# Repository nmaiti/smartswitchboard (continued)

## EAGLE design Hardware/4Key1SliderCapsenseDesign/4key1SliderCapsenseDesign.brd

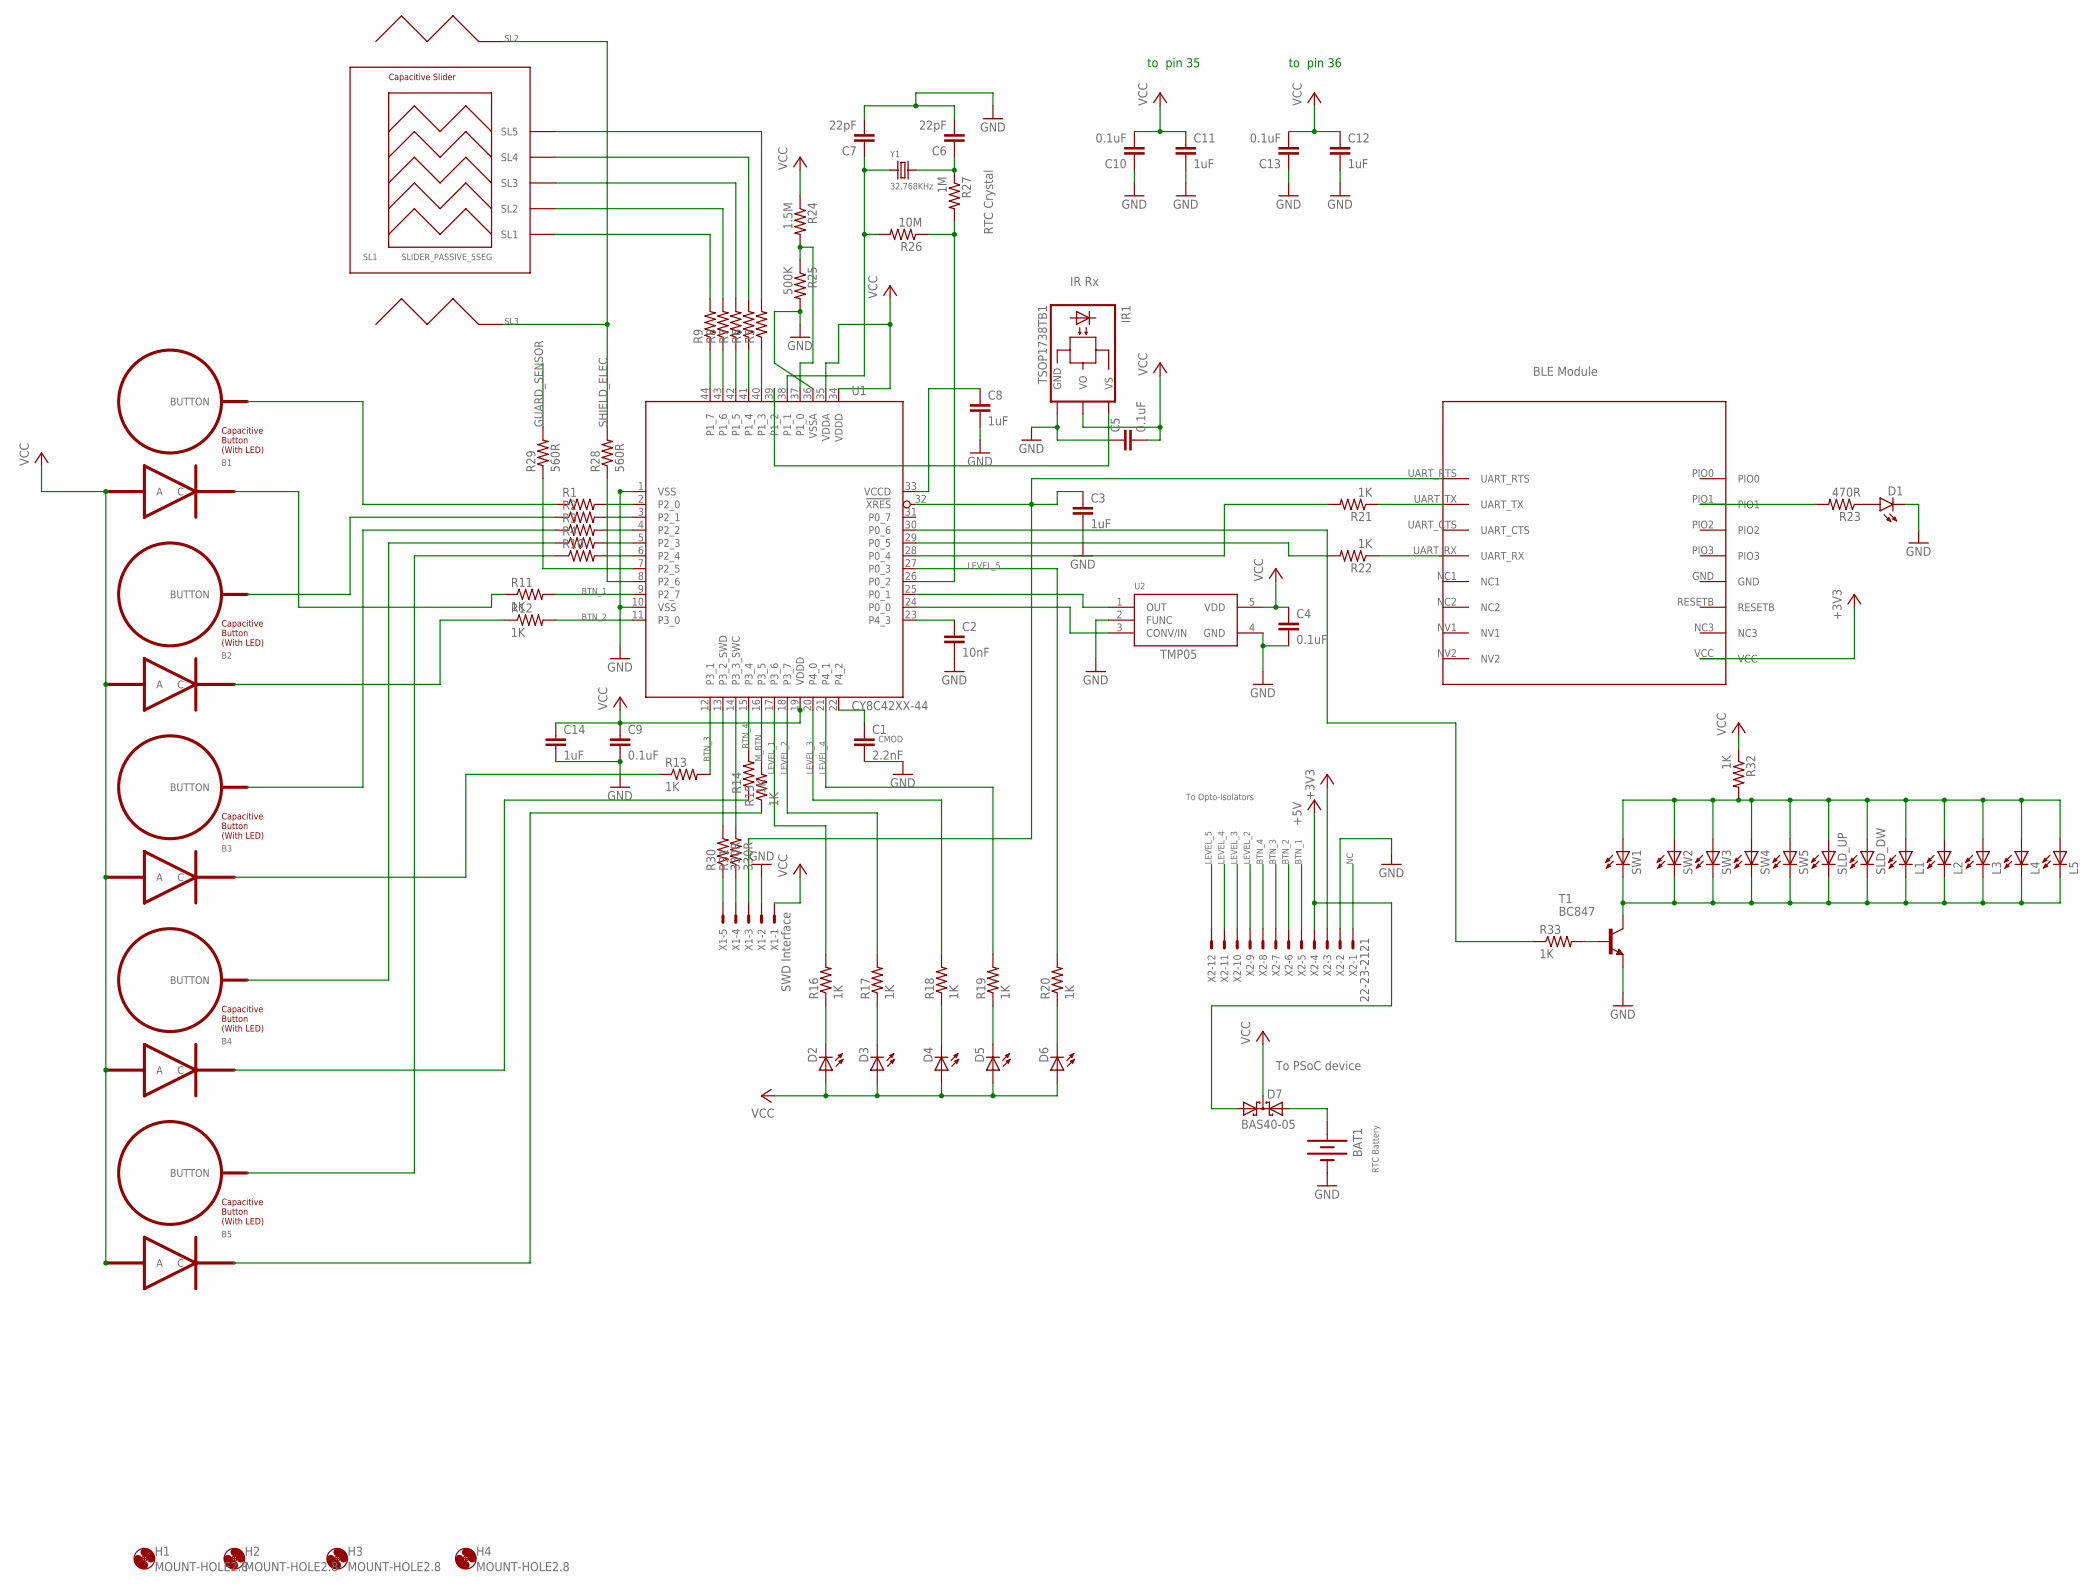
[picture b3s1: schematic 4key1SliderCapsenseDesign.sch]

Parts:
B1, B2, B3, B4, B5: BUTTON_PASSIVE_LED; BUTTON_PASSIVE_12MM_LED
BAT1: BATTERY245MM; BATTCON_245MM
C1: 2.2nF; 1206
C2: 10nF; 1206
C3, C8, C11, C12, C14: 1uF; 1206
C4, C5, C9, C10, C13: 0.1uF; 1206
C6, C7: 22pF; 1206
D1: LED1206-BOTTOM; LED-1206-BOTTOM
D2, D3, D4, D5, D6: LEDCHIP-LED0805; CHIP-LED0805
D7: BAS40-05; SOT23
H1, H2, H3, H4: MOUNT-HOLE2.8; 2,8
IR1: TSOP1738TB1; TSOP17_TB1
L1, L2, L3, L4, L5: LEDCHIPLED_1206; CHIPLED_1206
R1, R2, R3, R4, R5, R6, R7, R8, R9, R10: RESISTOR1206; 1206
R11, R12, R13, R14, R15, R16, R17, R18, R19, R20, R21, R22, R32, R33: 1K; 1206
R23: 470R; 1206
R24: 1.5M; 1206
R25: 500K; 1206
R26: 10M; 1206
R27: 1M; 1206
R28, R29: 560R; 1206
R30, R31: 330R; 1206
SL1: SLIDER_PASSIVE_5SEG; SLIDER_PASSIVE_5SEG_12MM
SL2, SL3: SLIDER_PASSIVE_1SEG; SLIDER_PASSIVE_1SEG_12MM
SLD_DW: LEDCHIPLED_1206; CHIPLED_1206
SLD_UP: LEDCHIPLED_1206; CHIPLED_1206
SW1, SW2, SW3, SW4, SW5: LEDCHIPLED_1206; CHIPLED_1206
T1: BC847; SOT23
U1: CY8C42XX-44; TQFP-10X10-44
U2: NCP1400A_STEPUP; SOT23-5
U$1: HM-11
X1: SWD Interface; 22-23-2051
X2: 22-23-2121
Y1: 32.768KHz; CRYSTAL_CYL_2X6MM_SMT

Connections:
+3V3: U$1.VCC, X2.3
+5V: D7.1 (A1), X2.4
BTN_1: R11.2, U1.9 (P2_7), X2.5
BTN_2: R12.2, U1.11 (P3_0), X2.6
BTN_3: R13.2, U1.12 (P3_1), X2.7
BTN_4: R14.2, U1.15 (P3_4), X2.8
GND: BAT1.2 (-), C1.2, C2.2, C3.2, C4.2, C5.1, C6.2, C7.2, C8.2, C9.2, C10.1, C11.2, C12.2, C13.1, C14.2, D1.C, IR1.GND, R25.2, T1.2 (E), U1.1 (VSS), U1.10 (VSS), U1.36 (VSSA), U2.2 (FUNC), U2.4 (GND), X1.2, X2.2
GUARD_SENSOR: R29.1, R29.2, U1.7 (P2_5)
LEVEL_1: R16.2, U1.17 (P3_6)
LEVEL_2: R17.2, U1.18 (P3_7), X2.9
LEVEL_3: R18.2, U1.20 (P4_0), X2.10
LEVEL_4: R19.2, U1.21 (P4_1), X2.11
LEVEL_5: R20.2, U1.27 (P0_3), X2.12
M_BTN: R15.2, U1.16 (P3_5)
unnamed: C1.1, U1.22 (P4_2)
unnamed: R1.2, U1.2 (P2_0)
unnamed: C2.1, U1.23 (P4_3)
unnamed: R2.2, U1.3 (P2_1)
unnamed: R3.2, U1.4 (P2_2)
unnamed: R4.2, U1.5 (P2_3)
unnamed: B1.BUTTON, R1.1
unnamed: B2.BUTTON, R2.1
unnamed: B3.BUTTON, R3.1
unnamed: B4.BUTTON, R4.1
unnamed: R10.2, U1.6 (P2_4)
unnamed: B5.BUTTON, R10.1
unnamed: R5.1, U1.40 (P1_3)
unnamed: R6.1, U1.41 (P1_4)
unnamed: R7.1, U1.42 (P1_5)
unnamed: R8.1, U1.43 (P1_6)
unnamed: R9.1, U1.44 (P1_7)
unnamed: R9.2, SL1.SL1
unnamed: R8.2, SL1.SL2
unnamed: R7.2, SL1.SL3
unnamed: R6.2, SL1.SL4
unnamed: R5.2, SL1.SL5
unnamed: R28.1, U1.8 (P2_6)
unnamed: B1.C, R11.1
unnamed: B2.C, R12.1
unnamed: B3.C, R13.1
unnamed: B4.C, R14.1
unnamed: B5.C, R15.1
unnamed: R30.2, U1.13 (P3_2_SWD)
unnamed: C8.1, U1.33 (VCCD)
unnamed: R30.1, X1.5
unnamed: R31.2, U1.14 (P3_3_SWC)
unnamed: R31.1, X1.4
unnamed: L1.A, L2.A, L3.A, L4.A, L5.A, R32.2, SLD_DW.A, SLD_UP.A, SW1.A, SW2.A, SW3.A, SW4.A, SW5.A
unnamed: D2.C, R16.1
unnamed: L1.C, L2.C, L3.C, L4.C, L5.C, SLD_DW.C, SLD_UP.C, SW1.C, SW2.C, SW3.C, SW4.C, SW5.C, T1.3 (C)
unnamed: D3.C, R17.1
unnamed: R33.2, T1.1 (B)
unnamed: BAT1.1 (+), D7.2 (A2)
unnamed: C3.1, U1.32 (!XRES), U$1.UART_RTS, X1.3
unnamed: R21.1, U$1.UART_TX
unnamed: R33.1, U1.30 (P0_6)
unnamed: R22.1, U$1.UART_RX
unnamed: R21.2, U1.28 (P0_4)
unnamed: R22.2, U1.29 (P0_5)
unnamed: D1.A, R23.1
unnamed: U1.24 (P0_0), U2.3 (CONV/IN)
unnamed: R23.2, U$1.PIO1
unnamed: U1.25 (P0_1), U2.1 (OUT)
unnamed: IR1.VS, U1.39 (P1_2)
unnamed: R24.2, R25.1, U1.37 (P1_0)
unnamed: R26.1, R27.2, U1.26 (P0_2)
unnamed: C6.1, R27.1, Y1.2
unnamed: C7.1, R26.2, U1.38 (P1_1), Y1.1
unnamed: D6.C, R20.1
unnamed: D5.C, R19.1
unnamed: D4.C, R18.1
NC: X2.1
SHIELD_ELEC: R28.2, SL2.S1, SL3.S1
VCC: B1.A, B2.A, B3.A, B4.A, B5.A, C4.1, C5.2, C9.1, C10.2, C11.1, C12.1, C13.2, C14.1, D2.A, D3.A, D4.A, D5.A, D6.A, D7.3 (C), IR1.VO, R24.1, R32.1, U1.19 (VDDD), U1.34 (VDDD), U1.35 (VDDA), U2.5 (VDD), X1.1

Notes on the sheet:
CMOD
TMP05
To Opto-Isolators
IR Rx
BLE Module
RTC Crystal
to pin 36
to pin 35
To PSoC device
RTC Battery

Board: 2 copper layers, 87 parts (35 on the bottom side), 73 nets, no tracks yet.

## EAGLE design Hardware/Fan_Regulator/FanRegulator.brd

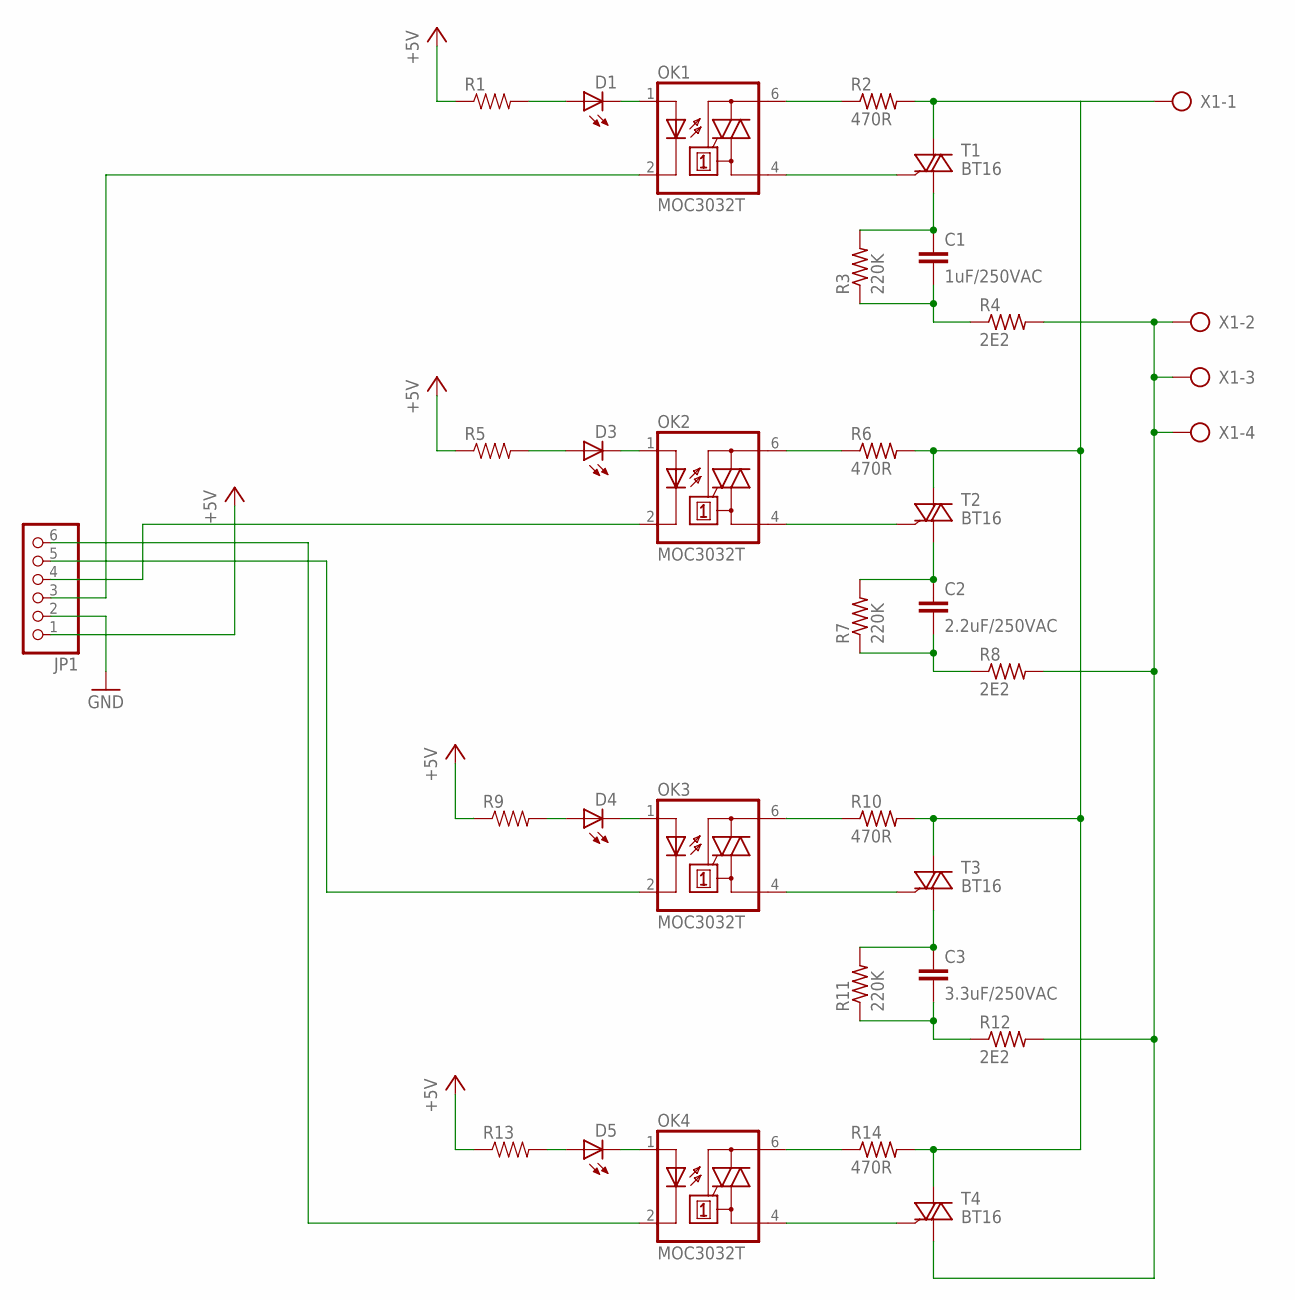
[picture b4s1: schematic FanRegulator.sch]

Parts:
C1: 1uF/250VAC; C27.5B9
C2: 2.2uF/250VAC; C27.5B9
C3: 3.3uF/250VAC; C27.5B9
D1, D3, D4, D5: LED3MM
JP1: PINHD-1X6; 1X06
OK1, OK2, OK3, OK4: MOC3032T; DIL06B
R1, R5, R9, R13: RESISTOR1206; 1206
R2, R6, R10, R14: 470R; R0207/1V
R3, R7, R11: 220K; R0207/1V
R4, R8, R12: 2E2; R0207/1V
T1, T2, T3, T4: BT16; TO220BV
X1: AK300/4

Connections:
+5V: JP1.1, R1.1, R5.1, R9.1, R13.1
GND: JP1.2
unnamed: OK1.6 (A2), R2.1
unnamed: OK1.4 (A1), T1.G
unnamed: D1.A, R1.2
unnamed: C1.1, R3.2, T1.T1 (A1)
unnamed: C1.2, R3.1, R4.1
unnamed: D1.K (C), OK1.1 (A)
unnamed: D3.A, R5.2
unnamed: JP1.3, OK1.2 (C)
unnamed: OK2.6 (A2), R6.1
unnamed: OK2.4 (A1), T2.G
unnamed: R2.2, R6.2, R10.2, R14.2, T1.T2 (A2), T2.T2 (A2), T3.T2 (A2), T4.T2 (A2), X1.1
unnamed: C2.1, R7.2, T2.T1 (A1)
unnamed: C2.2, R7.1, R8.1
unnamed: D3.K (C), OK2.1 (A)
unnamed: D4.A, R9.2
unnamed: JP1.4, OK2.2 (C)
unnamed: OK3.6 (A2), R10.1
unnamed: OK3.4 (A1), T3.G
unnamed: D4.K (C), OK3.1 (A)
unnamed: C3.1, R11.2, T3.T1 (A1)
unnamed: C3.2, R11.1, R12.1
unnamed: D5.A, R13.2
unnamed: D5.K (C), OK4.1 (A)
unnamed: JP1.5, OK3.2 (C)
unnamed: OK4.6 (A2), R14.1
unnamed: OK4.4 (A1), T4.G
unnamed: JP1.6, OK4.2 (C)
unnamed: R4.2, R8.2, R12.2, T4.T1 (A1), X1.2, X1.3, X1.4

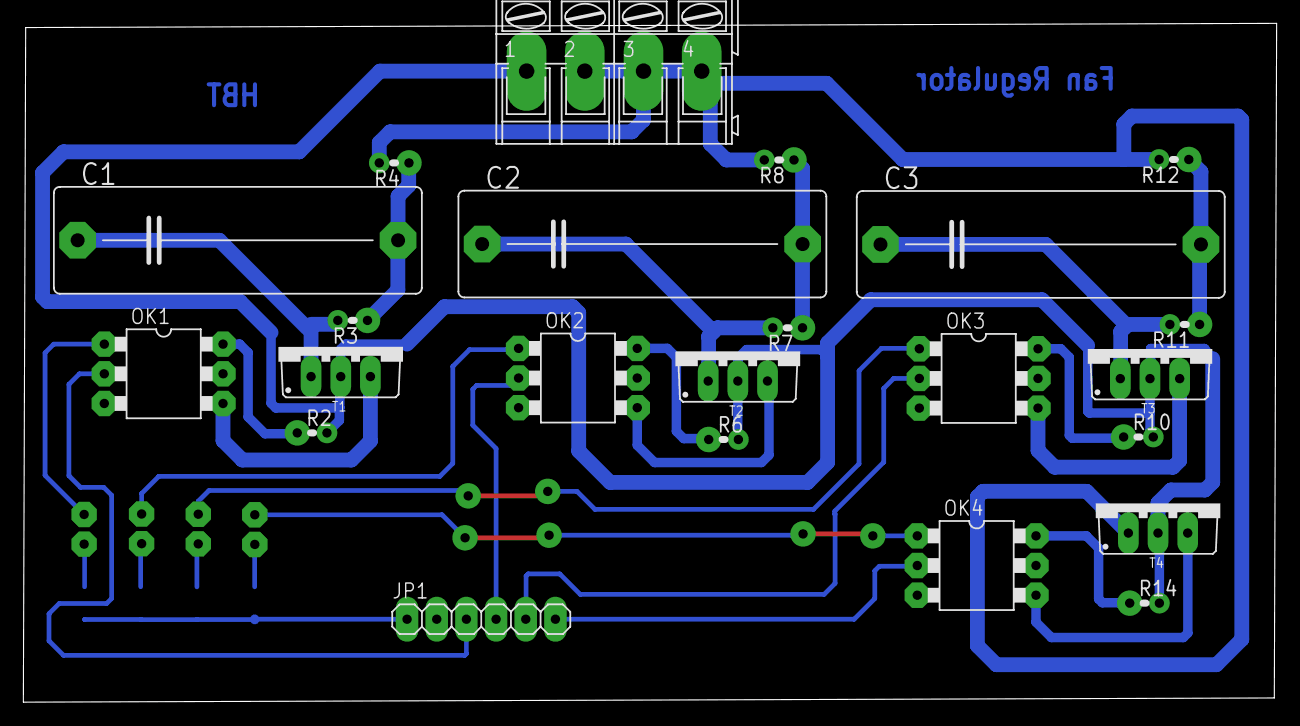
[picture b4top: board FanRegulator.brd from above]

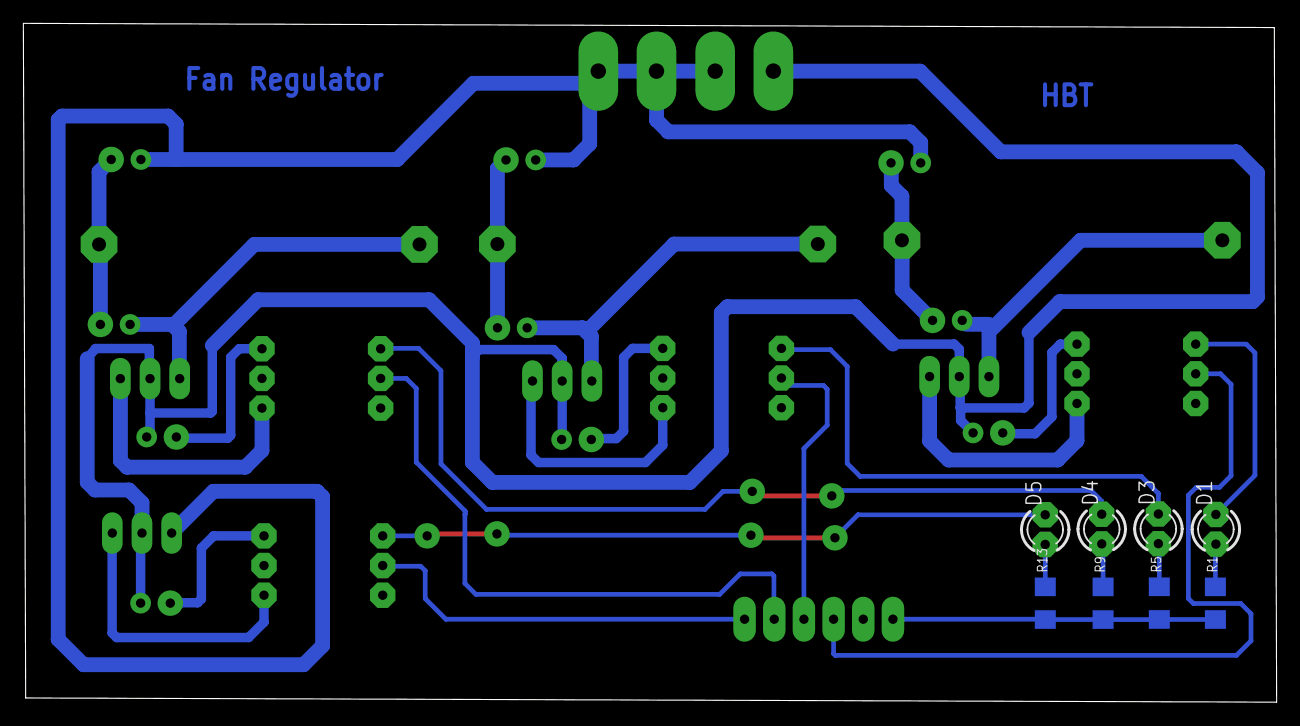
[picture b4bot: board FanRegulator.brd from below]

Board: 2 copper layers, 107.3 x 58.1 mm, 31 parts (8 on the bottom side), 29 nets.

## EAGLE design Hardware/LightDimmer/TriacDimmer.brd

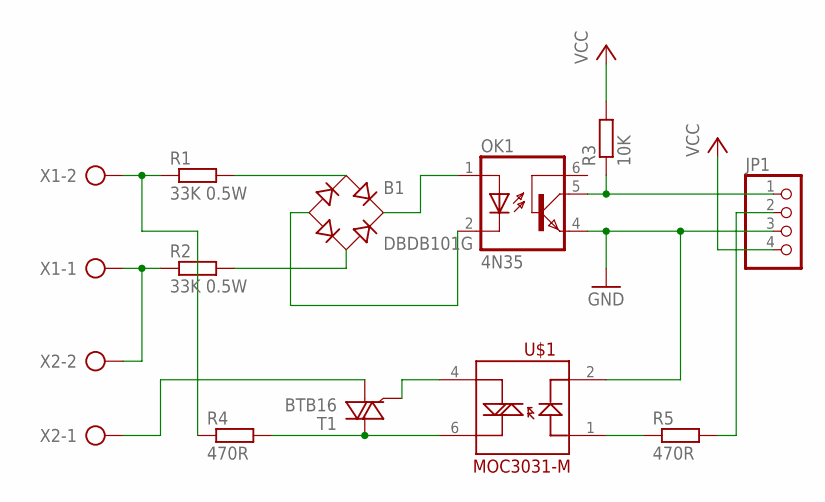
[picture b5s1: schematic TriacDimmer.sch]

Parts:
B1: DBDB101G; DB
JP1: PINHD-1X4; 1X04
OK1: 4N35; DIL06
R1, R2: 33K 0.5W; 0207/10
R3: 10K; 0207/10
R4, R5: 470R; 0207/10
T1: BTB16; TO220BV
U$1: MOC3031-M; DIL06
X1, X2: AK300/2

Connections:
GND: JP1.3, OK1.4 (EMI), U$1.2
unnamed: R1.1, R4.1, X1.2
unnamed: R2.1, X1.1, X2.2
unnamed: B1.AC1, R1.2
unnamed: B1.AC2, R2.2
unnamed: B1.+, OK1.1 (A)
unnamed: B1.-, OK1.2 (C)
unnamed: JP1.1, OK1.5 (COL), R3.1
unnamed: JP1.2, R5.2
unnamed: R4.2, T1.T2 (A2), U$1.6
unnamed: T1.G, U$1.4
unnamed: T1.T1 (A1), X2.1
unnamed: R5.1, U$1.1
VCC: JP1.4, R3.2

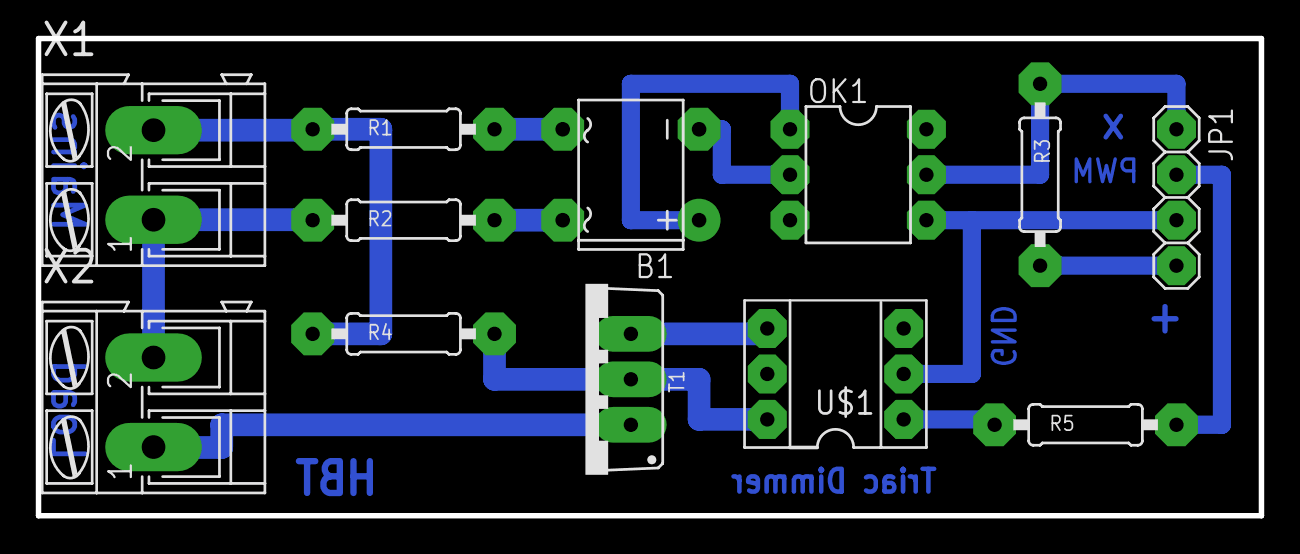
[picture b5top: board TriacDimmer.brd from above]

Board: 2 copper layers, 68.3 x 26.7 mm, 12 parts (0 on the bottom side), 14 nets.

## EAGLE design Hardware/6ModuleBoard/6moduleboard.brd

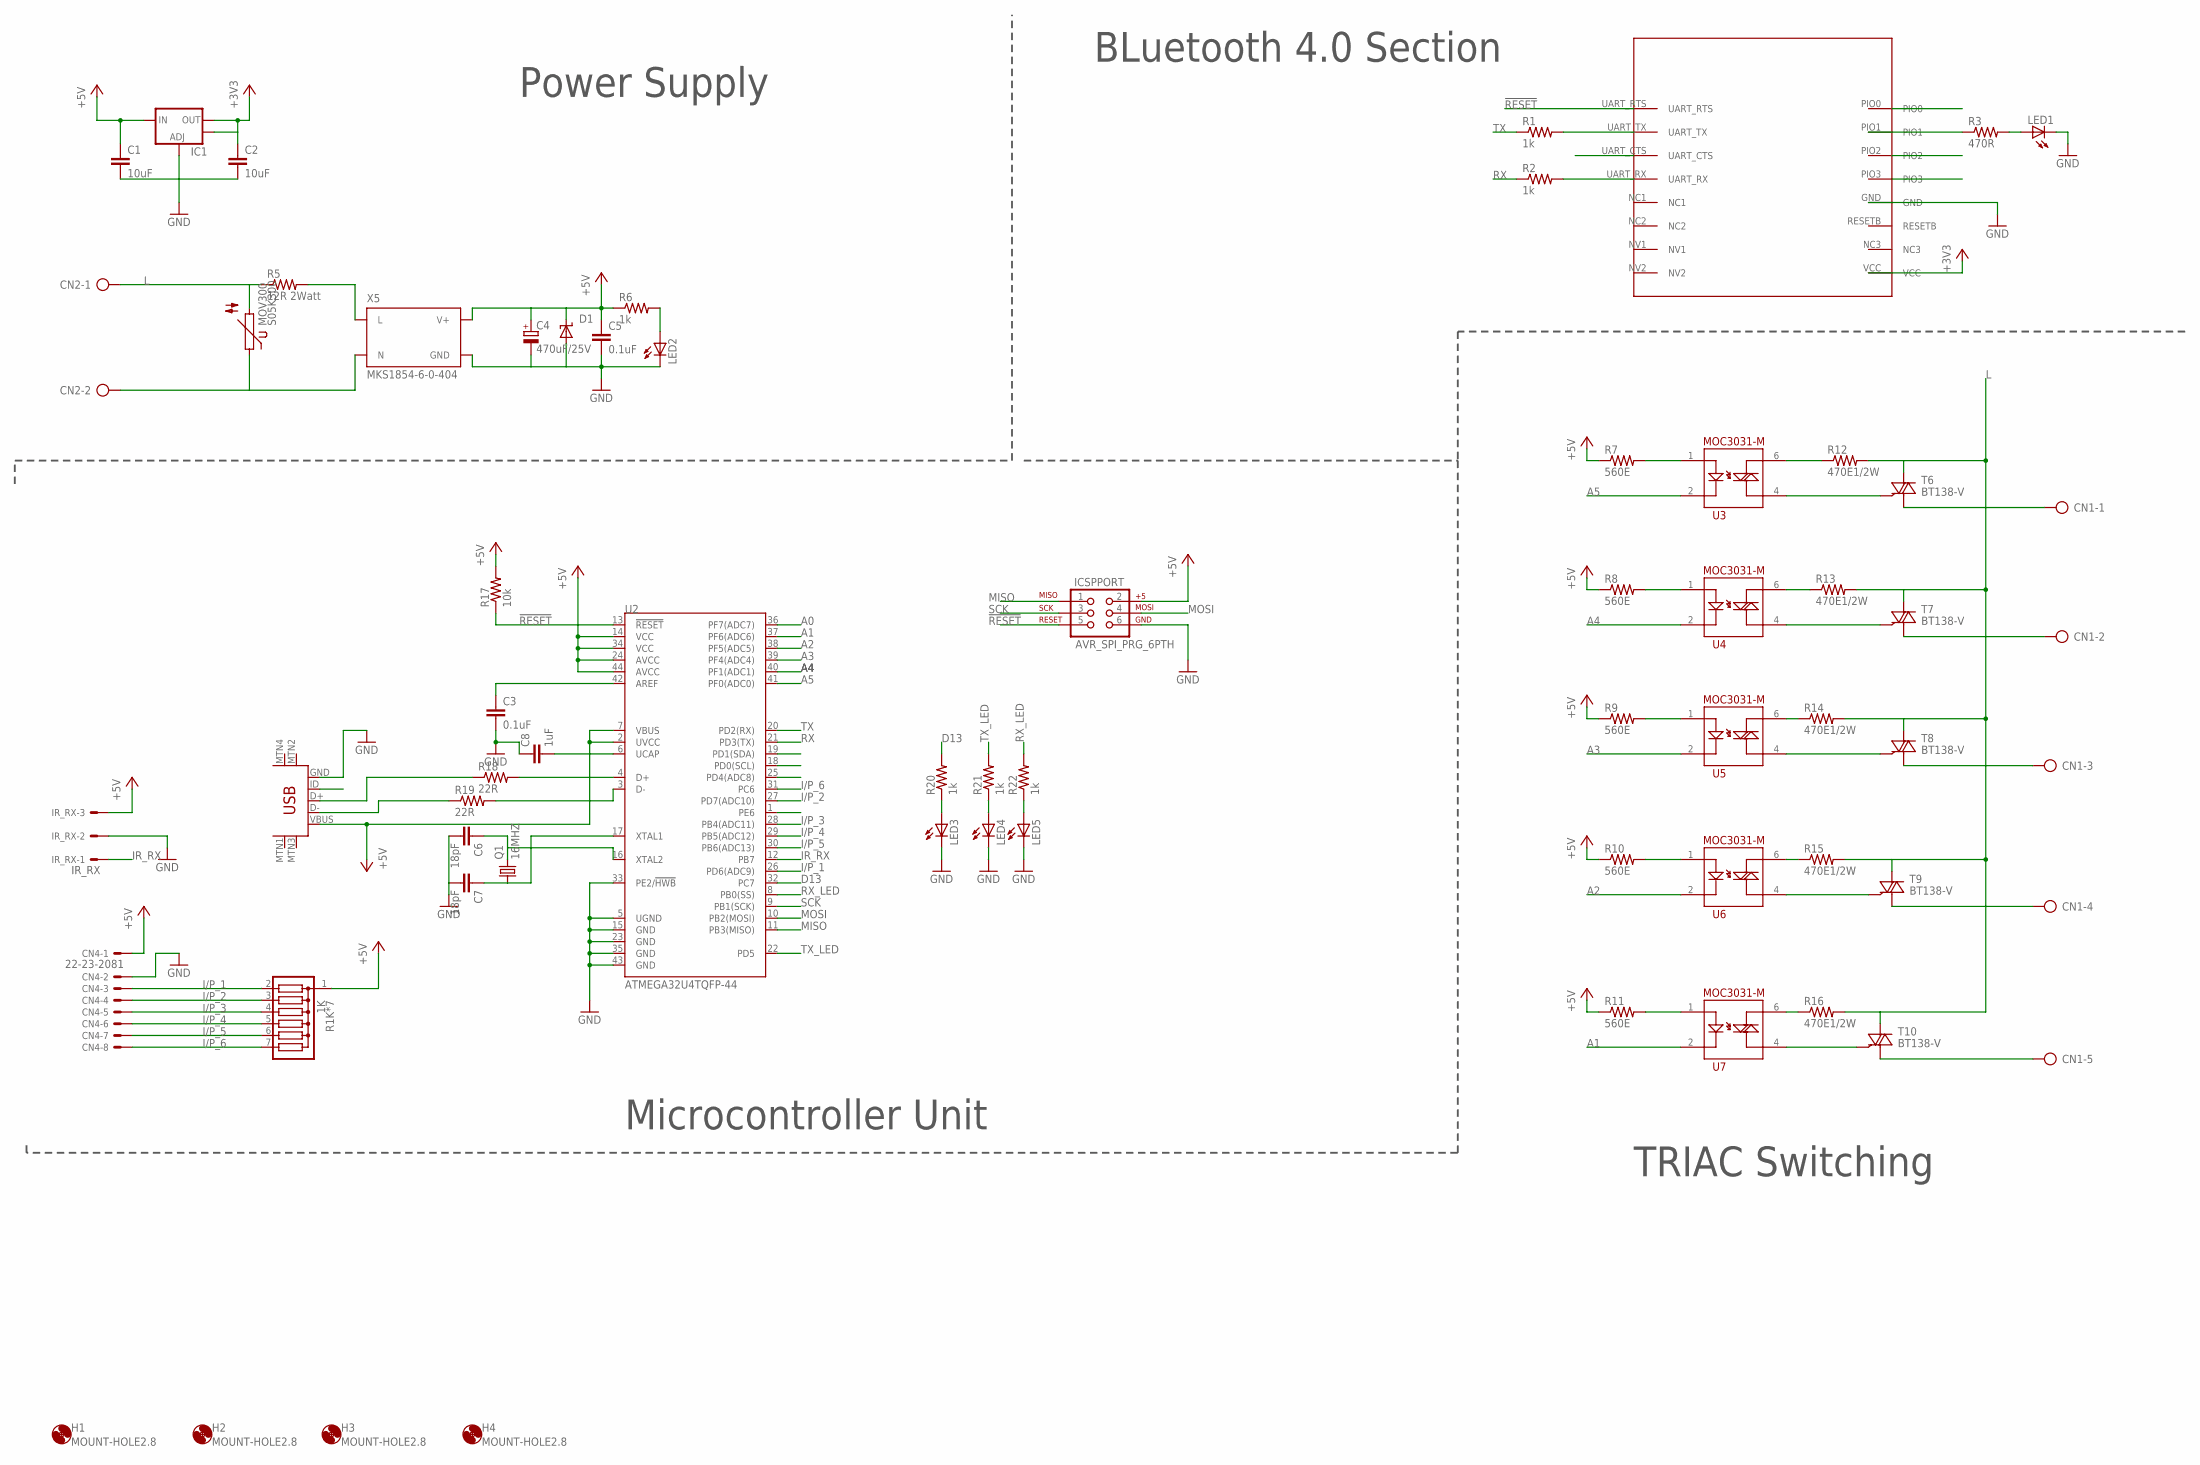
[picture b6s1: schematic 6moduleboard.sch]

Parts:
C1, C2: 10uF; 1206
C3, C5: 0.1uF; 1206
C4: 470uF/25V; E5-8,5
C6, C7: 18pF; 1206
C8: 1uF; 1206
CN1: AK300/5
CN2: AK300/2
CN4: 22-23-2081
D1: SUPPRESSOR-SMBJ; SMBJ
H1, H2, H3, H4: MOUNT-HOLE2.8; 2,8
IC1: V_REG_LM1117SOT223; SOT223
ICSPPORT: AVR_SPI_PRG_6PTH; 2X3
IR_RX: IR_RX; 22-23-2031
LED1, LED2, LED3, LED4, LED5: LEDSMT1206; 1206
MOV300: S05K300
Q1: 16MHZ; HC49UP
R1, R2, R6, R20, R21, R22: 1k; 1206
R1K*7: 1K; SIL7
R3: 470R; 1206
R5: 12R 2Watt; 0207/10
R7, R8, R9, R10, R11: 560E; 1206
R12, R13, R14, R15, R16: 470E1/2W; 0411V
R17: 10k; 1206
R18, R19: 22R; 1206
T6, T7, T8, T9, T10: BT138-V; TO220BV
U2: ATMEGA32U4TQFP-44; TQFP44
U3, U4, U5, U6, U7: MOC3083; DIL06
U8: USB-MINIB-5PIN; USB-MINIB
U$1: HM-11
X5: MKS1854-6-0-404

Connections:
!RESET: ICSPPORT.5, R17.1, U2.13 (!RESET), U$1.UART_RTS
+3V3: C2.1, IC1.2 (OUT), IC1.4 (OUT), U$1.VCC
+5V: C1.1, C4.+, C5.1, CN4.1, D1.C, IC1.3 (IN), ICSPPORT.2, IR_RX.3, R1K*7.1, R6.1, R7.1, R8.1, R9.1, R10.1, R11.1, R17.2, U2.2 (UVCC), U2.7 (VBUS), U2.14 (VCC), U2.24 (AVCC), U2.34 (VCC), U2.44 (AVCC), U8.VBUS, X5.3 (V+)
A0: U2.36 (PF7(ADC7))
A1: U2.37 (PF6(ADC6)), U7.2
A2: U2.38 (PF5(ADC5)), U6.2
A3: U2.39 (PF4(ADC4)), U5.2
A4: U2.40 (PF1(ADC1)), U4.2
A5: U2.41 (PF0(ADC0)), U3.2
D13: R20.2, U2.32 (PC7)
GND: C1.2, C2.2, C3.2, C4.-, C5.2, C6.2, C7.2, C8.1, CN4.2, D1.A, IC1.1 (ADJ), ICSPPORT.6, IR_RX.2, LED1.C, LED2.C, LED3.C, LED4.C, LED5.C, U2.5 (UGND), U2.15 (GND), U2.23 (GND), U2.33 (PE2/!HWB), U2.35 (GND), U2.43 (GND), U8.GND, U$1.GND, X5.4 (GND)
I/P_1: CN4.3, R1K*7.2, U2.26 (PD6(ADC9))
I/P_2: CN4.4, R1K*7.3, U2.27 (PD7(ADC10))
I/P_3: CN4.5, R1K*7.4, U2.28 (PB4(ADC11))
I/P_4: CN4.6, R1K*7.5, U2.29 (PB5(ADC12))
I/P_5: CN4.7, R1K*7.6, U2.30 (PB6(ADC13))
I/P_6: CN4.8, R1K*7.7, U2.31 (PC6)
IR_RX: IR_RX.1, U2.12 (PB7)
L: CN2.1, MOV300.2, R5.1, R12.2, R13.2, R14.2, R15.2, R16.2, T6.T2 (A2), T7.T2 (A2), T8.T2 (A2), T9.T2 (A2), T10.T2 (A2)
MISO: ICSPPORT.1, U2.11 (PB3(MISO))
MOSI: ICSPPORT.4, U2.10 (PB2(MOSI))
unnamed: R3.1, U$1.PIO1
unnamed: LED1.A, R3.2
unnamed: R5.2, X5.1 (L)
unnamed: CN2.2, MOV300.1, X5.2 (N)
unnamed: R1.2, U$1.UART_TX
unnamed: R2.2, U$1.UART_RX
unnamed: CN1.1, T6.T1 (A1)
unnamed: CN1.2, T7.T1 (A1)
unnamed: R7.2, U3.1
unnamed: R12.1, U3.6
unnamed: R8.2, U4.1
unnamed: LED2.A, R6.2
unnamed: R9.2, U5.1
unnamed: R10.2, U6.1
unnamed: R11.2, U7.1
unnamed: LED4.A, R21.1
unnamed: LED5.A, R22.1
unnamed: R13.1, U4.6
unnamed: R14.1, U5.6
unnamed: R15.1, U6.6
unnamed: R16.1, U7.6
unnamed: T6.G, U3.4
unnamed: T7.G, U4.4
unnamed: T8.G, U5.4
unnamed: C8.2, U2.6 (UCAP)
unnamed: T9.G, U6.4
unnamed: C3.1, U2.42 (AREF)
unnamed: T10.G, U7.4
unnamed: CN1.5, T10.T1 (A1)
unnamed: CN1.3, T8.T1 (A1)
unnamed: CN1.4, T9.T1 (A1)
unnamed: R18.2, U2.4 (D+)
unnamed: R19.2, U2.3 (D-)
unnamed: R18.1, U8.D+
unnamed: R19.1, U8.D-
unnamed: C6.1, Q1.2, U2.16 (XTAL2)
unnamed: C7.1, Q1.1, U2.17 (XTAL1)
unnamed: LED3.A, R20.1
RX: R2.1, U2.21 (PD3(TX))
RX_LED: R22.2, U2.8 (PB0(SS))
SCK: ICSPPORT.3, U2.9 (PB1(SCK))
TX: R1.1, U2.20 (PD2(RX))
TX_LED: R21.2, U2.22 (PD5)

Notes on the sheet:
Power Supply
BLuetooth 4.0 Section
Microcontroller Unit
TRIAC Switching

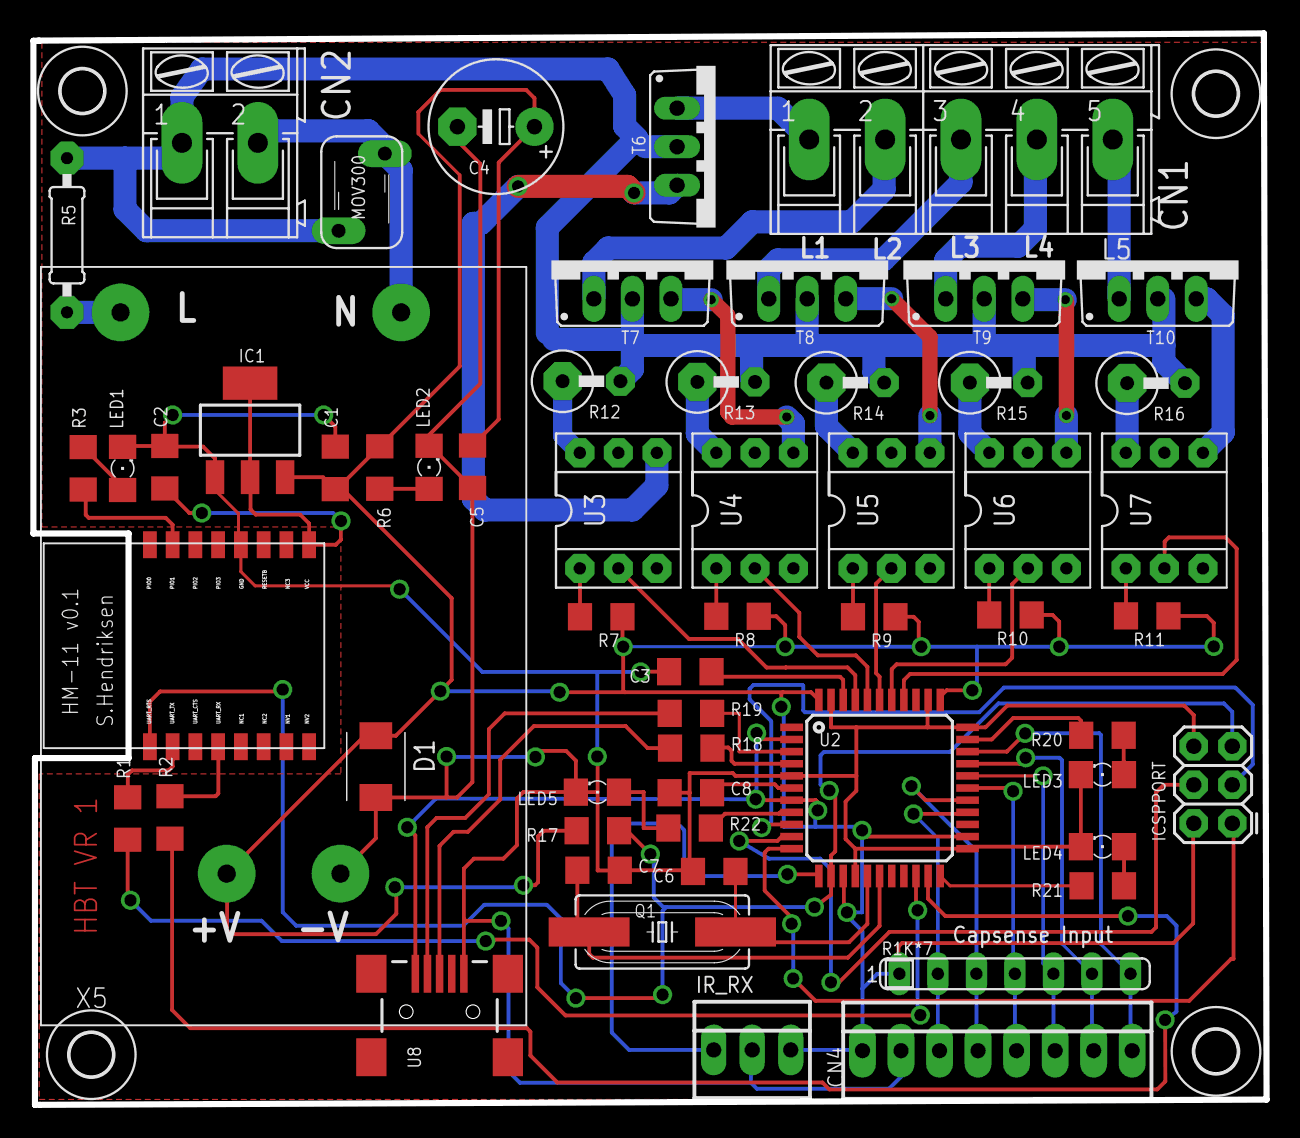
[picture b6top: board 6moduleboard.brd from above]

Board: 2 copper layers, 81.3 x 70.6 mm, 62 parts (0 on the bottom side), 63 nets.

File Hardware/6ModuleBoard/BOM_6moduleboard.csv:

"Part";"Value";"Device";"Package";"Description";"MF";"MPN";"OC_FARNELL";"OC_NEWARK";"PROD_ID";"VALUE";
"C1";"10uF";"10UF-6.3V-20%(1206)";"1206";"CAP-10057";"";"";"";"";"CAP-10057";"10uF";
"C2";"10uF";"10UF-6.3V-20%(1206)";"1206";"CAP-10057";"";"";"";"";"CAP-10057";"10uF";
"C3";"0.1uF";"CAP1206";"1206";"Capacitor";"";"";"";"";"";"";
"C4";"470uF/25V";"CPOL-EUE5-8.5";"E5-8,5";"POLARIZED CAPACITOR, European symbol";"";"";"";"";"";"";
"C5";"0.1uF";"1.0UF50V10%(1206)";"1206";"CAP-09822";"";"";"";"";"CAP-09822";"1.0uF";
"C6";"18pF";"CAP1206";"1206";"Capacitor";"";"";"";"";"";"";
"C7";"18pF";"CAP1206";"1206";"Capacitor";"";"";"";"";"";"";
"C8";"1uF";"CAP1206";"1206";"Capacitor";"";"";"";"";"";"";
"CN1";"";"AK300/5";"AK300/5";"CONNECTOR";"";"";"unknown";"unknown";"";"";
"CN2";"";"AK300/2";"AK300/2";"CONNECTOR";"";"";"unknown";"unknown";"";"";
"CN4";"22-23-2081";"22-23-2081";"22-23-2081";".100" (2.54mm) Center Header - 8 Pin";"MOLEX";"22-23-2081";"1756826";"01C7592";"";"";
"D1";"";"SUPPRESSOR-SMBJ";"SMBJ";"Suppressor diode";"";"";"";"";"";"";
"H1";"MOUNT-HOLE2.8";"MOUNT-HOLE2.8";"2,8";"MOUNTING HOLE with drill center marker";"";"";"";"";"";"";
"H2";"MOUNT-HOLE2.8";"MOUNT-HOLE2.8";"2,8";"MOUNTING HOLE with drill center marker";"";"";"";"";"";"";
"H3";"MOUNT-HOLE2.8";"MOUNT-HOLE2.8";"2,8";"MOUNTING HOLE with drill center marker";"";"";"";"";"";"";
"H4";"MOUNT-HOLE2.8";"MOUNT-HOLE2.8";"2,8";"MOUNTING HOLE with drill center marker";"";"";"";"";"";"";
"IC1";"";"V_REG_LM1117SOT223";"SOT223";"Voltage Regulator LM1117";"";"";"";"";"VREG-08170";"";
"ICSPPORT";"AVR_SPI_PRG_6PTH";"AVR_SPI_PRG_6PTH";"2X3";"AVR ISP 6 Pin";"";"";"";"";"";"";
"IR_RX";"IR_RX";"22-23-2031";"22-23-2031";".100" (2.54mm) Center Header - 3 Pin";"MOLEX";"22-23-2031";"1462950";"30C0862";"";"";
"LED1";"";"LEDSMT1206";"1206";"LED";"";"";"";"";"";"";
"LED2";"";"LEDSMT1206";"1206";"LED";"";"";"";"";"";"";
"LED3";"";"LEDSMT1206";"1206";"LED";"";"";"";"";"";"";
"LED4";"";"LEDSMT1206";"1206";"LED";"";"";"";"";"";"";
"LED5";"";"LEDSMT1206";"1206";"LED";"";"";"";"";"";"";
"MOV300";"S05K300";"S05K300";"S05K300";"VARISTOR";"";"";"";"";"";"";
"Q1";"16MHZ";"CRYSTALHC49UP";"HC49UP";"CRYSTAL";"";"";"unknown";"unknown";"";"";
"R1";"1k";"RESISTOR1206";"1206";"Resistor";"";"";"";"";"";"";
"R1K*7";"1K";"G06R";"SIL7";"SIL RESISTOR";"";"";"unknown";"unknown";"";"";
"R2";"1k";"RESISTOR1206";"1206";"Resistor";"";"";"";"";"";"";
"R3";"470R";"RESISTOR1206";"1206";"Resistor";"";"";"";"";"";"";
"R5";"12R 2Watt";"R-US_0207/10";"0207/10";"RESISTOR, American symbol";"";"";"";"";"";"";
"R6";"1k";"RESISTOR1206";"1206";"Resistor";"";"";"";"";"";"";
"R7";"560E";"RESISTOR1206";"1206";"Resistor";"";"";"";"";"";"";
"R8";"560E";"RESISTOR1206";"1206";"Resistor";"";"";"";"";"";"";
"R9";"560E";"RESISTOR1206";"1206";"Resistor";"";"";"";"";"";"";
"R10";"560E";"RESISTOR1206";"1206";"Resistor";"";"";"";"";"";"";
"R11";"560E";"RESISTOR1206";"1206";"Resistor";"";"";"";"";"";"";
"R12";"470E1/2W";"R-US_0411/3V";"0411V";"RESISTOR, American symbol";"";"";"";"";"";"";
"R13";"470E1/2W";"R-US_0411/3V";"0411V";"RESISTOR, American symbol";"";"";"";"";"";"";
"R14";"470E1/2W";"R-US_0411/3V";"0411V";"RESISTOR, American symbol";"";"";"";"";"";"";
"R15";"470E1/2W";"R-US_0411/3V";"0411V";"RESISTOR, American symbol";"";"";"";"";"";"";
"R16";"470E1/2W";"R-US_0411/3V";"0411V";"RESISTOR, American symbol";"";"";"";"";"";"";
"R17";"10k";"RESISTOR1206";"1206";"Resistor";"";"";"";"";"";"";
"R18";"22R";"RESISTOR1206";"1206";"Resistor";"";"";"";"";"";"";
"R19";"22R";"RESISTOR1206";"1206";"Resistor";"";"";"";"";"";"";
"R20";"1k";"RESISTOR1206";"1206";"Resistor";"";"";"";"";"";"";
"R21";"1k";"RESISTOR1206";"1206";"Resistor";"";"";"";"";"";"";
"R22";"1k";"RESISTOR1206";"1206";"Resistor";"";"";"";"";"";"";
"T6";"BT138-V";"BT138-V";"TO220BV";"TRIAC";"";"";"";"";"";"";
"T7";"BT138-V";"BT138-V";"TO220BV";"TRIAC";"";"";"";"";"";"";
"T8";"BT138-V";"BT138-V";"TO220BV";"TRIAC";"";"";"";"";"";"";
"T9";"BT138-V";"BT138-V";"TO220BV";"TRIAC";"";"";"";"";"";"";
"T10";"BT138-V";"BT138-V";"TO220BV";"TRIAC";"";"";"";"";"";"";
"U$1";"HM-11";"HM-11";"HM-11";"";"";"";"";"";"";"";
"U2";"ATMEGA32U4TQFP-44";"ATMEGA32U4TQFP-44";"TQFP44";"Atmel 44-pin 8-bit Microcontroller with 32KBytes of ISP Flash and USB Controller";"";"";"";"";"";"";
"U3";"MOC3083";"MOC3031-M";"DIL06";"Opto-isolated TRIAC";"";"";"";"";"";"";
"U4";"MOC3083";"MOC3031-M";"DIL06";"Opto-isolated TRIAC";"";"";"";"";"";"";
"U5";"MOC3083";"MOC3031-M";"DIL06";"Opto-isolated TRIAC";"";"";"";"";"";"";
"U6";"MOC3083";"MOC3031-M";"DIL06";"Opto-isolated TRIAC";"";"";"";"";"";"";
"U7";"MOC3083";"MOC3031-M";"DIL06";"Opto-isolated TRIAC";"";"";"";"";"";"";
"U8";"USB-MINIB-5PIN";"USB-MINIB-5PIN";"USB-MINIB";"Mini-USB "B" connector with 5th pin broken out.";"";"";"";"";"";"";
"X5";"MKS1854-6-0-404";"MKS1854-6-0-404";"MKS1854-6-0-404";"Serie MKS 1850 Lötstifte In-line, Raster 2.5 mm, Stiftwannen, stehend, mit Rastlasche";"";"";"1141862";"unknown";"";"";
